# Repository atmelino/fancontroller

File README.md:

<h3>ESPHome based PWM fan controller</h3>
This fan controller uses the ESP32 Control Board Ver. 2.1 <br>
<a href="https://www.tindie.com/products/esp32/esp32-control-board-ver-21/">
https://www.tindie.com/products/esp32/esp32-control-board-ver-21/</a><br>
and adds an expansion module with a display and two rotary encoders.<br>
<br>
The fan controller works without any USB or Internet connection and allows the user to view
all relevant data and set all necessary parameters.<br>
Additionally, the user may connect to the module via Wifi and remotely view more data and change settings, if desired.<br><br>

<div align="center">

</div>

The left button changes the temperature at which the fan turns off<br>
the right button changes the temperature at which the fan runs at full speed.<br>
<div align="center">
    
</div>
<br>
<h4>Circuit Diagram</h4>
<div align="center">
    
</div>
<br>
<h4>Parts</h4>

<a href="https://www.amazon.com/dp/B07T3672VK">
https://www.amazon.com/dp/B07T3672VK</a><br>
<br>

<a href="https://www.amazon.com/dp/B0C9LJ898Z">
https://www.amazon.com/dp/B0C9LJ898Z</a><br>

<h4>Source Code</h4>
<a href="https://github.com/atmelino/fancontroller/tree/main/sourcecode/ESPHome">
https://github.com/atmelino/fancontroller/tree/main/sourcecode/ESPHome</a><br>

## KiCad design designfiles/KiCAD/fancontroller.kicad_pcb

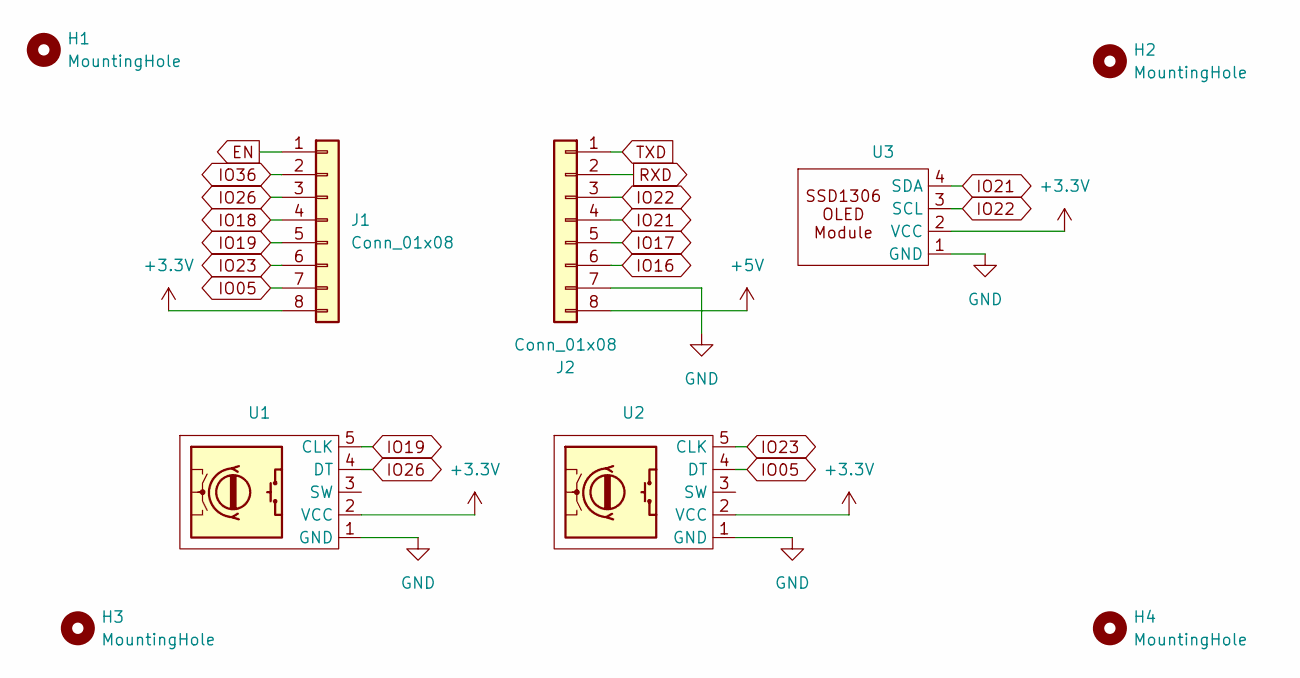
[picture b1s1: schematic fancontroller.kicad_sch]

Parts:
H1, H2, H3, H4: MountingHole; MountingHole_3.2mm_M3
J1, J2: Conn_01x08; PinHeader_1x08_P2.54mm_Vertical_largepads
U1, U2: PinHeader_1x05_P2.54mm_Vertical_largepads
U3: PinHeader_1x04_P2.54mm_Vertical_longpads

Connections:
+3.3V: J1.8, U1.2 (VCC), U2.2 (VCC), U3.2 (VCC)
+5V: J2.8
EN: J1.1
GND: J2.7, U1.1 (GND), U2.1 (GND), U3.1 (GND)
IO05: J1.7, U2.4 (DT)
IO16: J2.6
IO17: J2.5
IO18: J1.4
IO19: J1.5, U1.5 (CLK)
IO21: J2.4, U3.4 (SDA)
IO22: J2.3, U3.3 (SCL)
IO23: J1.6, U2.5 (CLK)
IO26: J1.3, U1.4 (DT)
IO36: J1.2
RXD: J2.2
TXD: J2.1

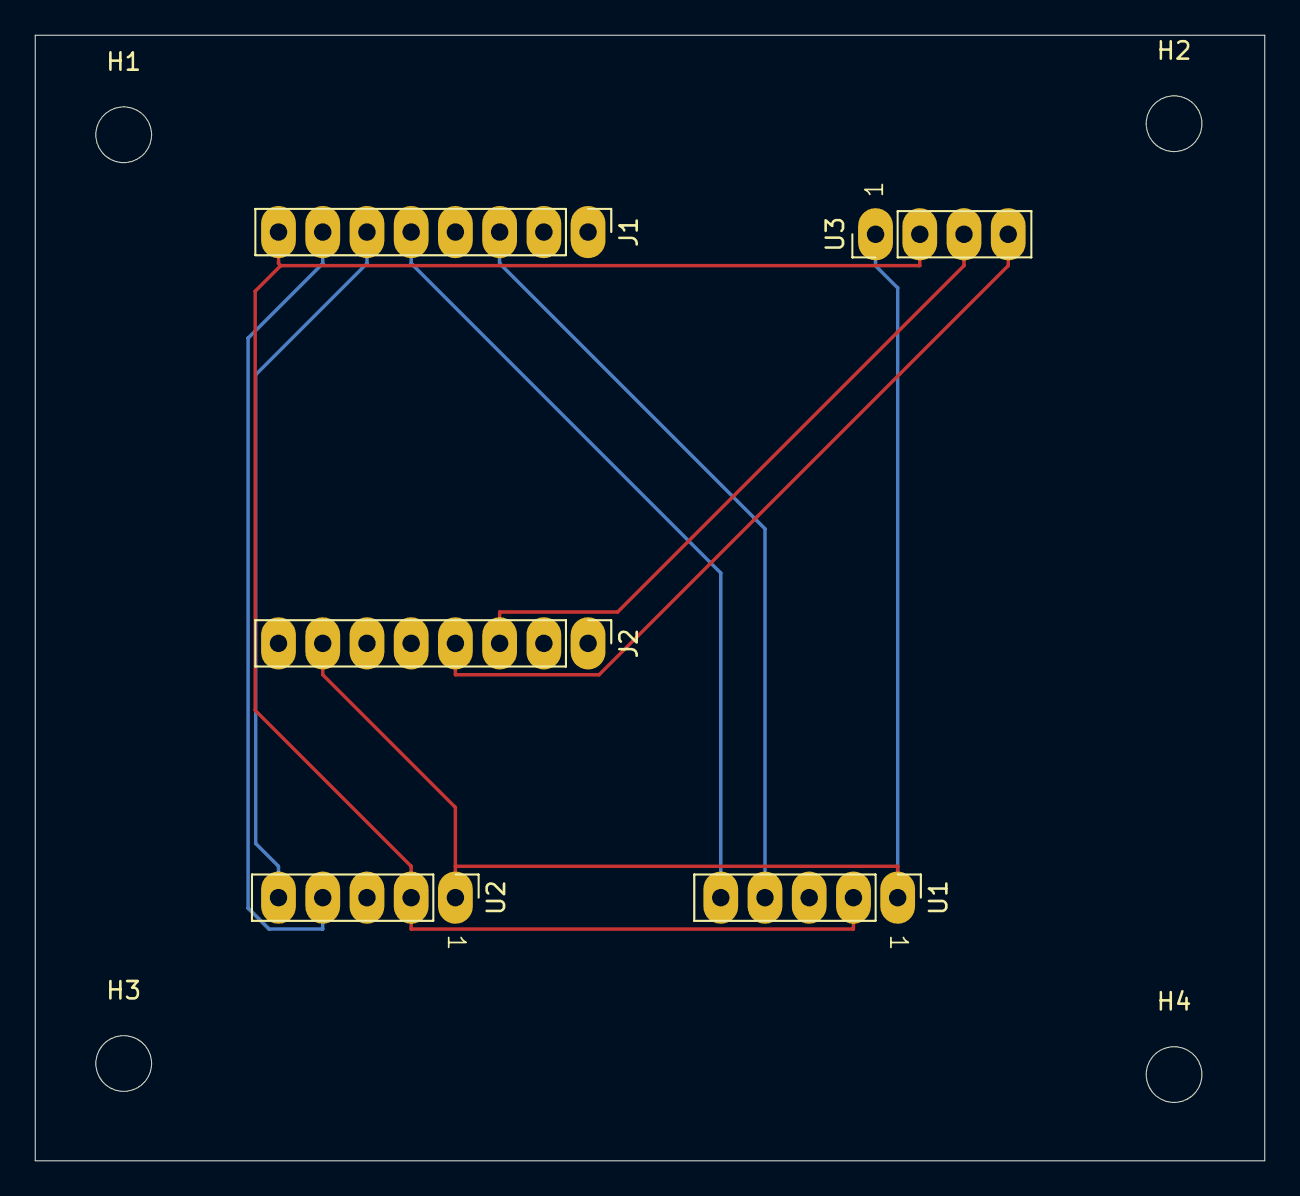
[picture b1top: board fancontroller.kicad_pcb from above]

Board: 2 copper layers, 70.6 x 64.6 mm, 9 parts (0 on the bottom side), 8 nets.
